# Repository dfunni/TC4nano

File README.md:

# TC4nano
The TC4nano is an Arduino Nano shield for termperature logging (up to 4 thermocouples) and PID control of a resistive heating element for use in home coffee roasting (based off of the TC4 Arduino Uno shield design copyright 2014 MLG Properties LLC and bvwelch.com CC-BY). The TC4nano includes one onboard SSR for heater control via slow PWM. Forced air is recommended for cooling the SSR in configurations drawing 10A or above.

### CONTENTS:
1. Configuring Artiasn
2. Updating TC4 Firmware
3. Troubleshooting

The TC4nano is pre-configured for the Artisan roaster-scope software using the aArtisanQ_PID_6_2_3 by Jim Gallt and Brad
Collins provided under BSD Liscense.

TC4 firmware can be found at:
https://github.com/greencardigan/TC4-shield

Artisan can be found at:	
https://github.com/artisan-roaster-scope

Artisan installation instructions:
https://github.com/artisan-roaster-scope/artisan/blob/master/wiki/Installation.md

## 1. CONFIGURING ARTISAN

### General Config
The configuration below assumes use with Poppery I roaster and no fan control through Artisan. 

For Poppery II or other DC fan systems, fan control can be added by connecting a DC motor driver to the IO3 jumper. For AC fan control, zero cross detection circuitry and an additional random fire SSR are required as well as reflashing the Arduino firmware with different configuration settings. For Artisan configuration with fan control see the setup described here: https://www.youtube.com/watch?v=0-Co-pXF2NM. 

#### Config > Device...

ET/BT tab:
- select TC4 radio button
- ET Channel - 2
- BT Channel - 1
- AT Channel - None
- PID Firmware - unchecked
- Control - checked
- Curves: ET - unchecked BT - checked
- LCDs: ET - unchecked BT - checked Swap - unchecked

Extra Devices tab:
- Add two devices

Device 1: 
- Device - ArduinoTC4 56 
- Label1 - "Heater" 

Device 2:
- Device - ArduinoTC4 78
- Label1 - "SV" 
- Label2 - "AT"

Note: after clicking "OK" in the Device menu the Port menu will automatically pop up. Prior to each roast session ensure the port reflects the correct Arduino.

#### Config > Sampling Interval 
- set to "1.0" seconds

#### Config > Curves... > RoR tab
- check the boxes for curves and LCDs you want to view and check projection

#### Config > Events

Config tab:
- Annotations - check
- 1 - uncheck - Fan
- 2 - check - Heater
- 3 - uncheck - Damper
- 4 - uncheck - Burner
- Auto CHARGE/Auto Drop/Mark MET/Show Time Guide - uncheck

Buttons tab:
- add one button
- Label - "Heater Off"
- Type - Heater
- Value - 0
- Action - Serial Command
- Documentation - "OT1;0"
- Visibility - ON

Sliders tab:
- In the heater row set the following to:
- Heater - check
- Action - Serial Command
- Command - "OT1;{}"
- Offset - 0.0
- Factor - 1
- Min - 0
- Max - 100
- Fan - uncheck
- Damper - uncheck
- Burner - uncheck

#### Config > Temperature
- Select Fahrenheit or Celcius mode

### PID Config

Click the blue CONTROL button (ensure Control is checked under Config > Device)

Recommended starting PID parameters:

|            | kp  | ki   | kd  |
|------------|-----|------|-----|
| Poppery I  | 2.2 | 0.08 | 20  |
| Poppery II | 1.3 | 0.06 | 4.5 |

- Source - BT

Target:
- Positive - Heater
- Negative - None

Set Value:
- Mode - Background (ensure background profile is loaded prior to roasting)
- Lookahead - 10s (adjust as necessary)

- Start PID on CHARGE - check

### Creating a Profile

#### Tools > Designer

Adjust the circles to the desired locations, add or delete points as necessary.

When profile is complete go to Tools > Designer (uncheck) and proile will be
loaded onto the graph.

Hit the RESET button, then save the profile to your Profiles directory.

### Loading a Background Profile

#### Roast > Background

- Show - check
- BT - check
- All others - uncheck
- Align - CHARGE
- Load - select a saved profile from your profile directory

## 2. UPDATING TC4 FIRMWARE

The latest version of the TC4 firmware can be found on github. Version 
6.6 zip file can be found at:
https://github.com/greencardigan/TC4-shield/tree/master/applications/Artisan/aArtisan_PID/tags/REL_aArtisanQ_PID_6_6

Once downloaded open aArtisanQ_PID.ino in the Arduino IDE 
(https://www.arduino.cc). This will open all of the other files from the
aArtisanQ_PID folder as seperate tabs in the IDE.

Select the user.h tab and to choose the options you wish to enable by 
uncommenting/commenting the options in this file.

- Under "Base configuration" ensure CONFIG_PWM is selected as the 
TC4nano does not include a ZCD.

- Under "Tempreature Unit" comment out CELCIUS if Fahrenhiet is desired.

When all appropriate changes are made, connect the Arduino to the computer and
select the following settings from the menu bar:

- Tools > Board > Arduino Nano
- Tools > Processor > ATMega328P (Old Bootloader)
- Tools > Port > /dev/cu.YOUR_ARDUINO

Finally, flash the Adduino Nano by clicking the upload (forward arrow) button 
in the Arduino IDE. A display of the progress will appear in the command prompt
at the bottom of the IDE and "Done Uploading" will display when it completes 
sucessfully.

## 3. TROUBLESHOOTING:

### Generic Arduino Not Recognized (macOS)

Copy and paste these commands into terminal one by one 
(to open terminal press command+space and type 'terminal', then hit enter):

First check to see if homebrew is installed

    brew --version

If it is not installed (ie you get an output that is something other than
the version of homebrew) run the following commmand

    /usr/bin/ruby -e "$(curl -fsSL https://raw.githubusercontent.com/Homebrew/install/master/install)"

Then run the following two commands to install the CH34x drivers needed
to use the generic arduino nano

    brew tap mengbo/ch340g-ch34g-ch34x-mac-os-x-driver https://github.com/mengbo/ch340g-ch34g-ch34x-mac-os-x-driver
    brew cask install wch-ch34x-usb-serial-driver

Now restart your computer, and see if Artisan recognizes the arduino.
Alternately, you can enter the following in the terminal and look for an output
that is not an error.

    ls /dev/cu.usb* /dev/cu.wch*

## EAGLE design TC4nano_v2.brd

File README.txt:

# TC4nano
The configuration specified in this document is for the TC4nano which uses
one SSR for heater control (no fan control) and logs BT only.

CONTENTS:
Configuring Artiasn
- General Config
- PID Config
- Creating a Profile
- Loading a Background Profile
Updating TC4 Firmware
Troubleshooting
- Generic Arduino Nano Not Recognized

The TC4nano is configured for the Artisan roaster-scope software. The latest 
version can be found at:	
https://artisan-roasterscope.blogspot.com

Artisan installation instructions:
https://github.com/artisan-roaster-scope/artisan/blob/master/wiki/Installation.md

The TC4nano comes preloaded with aArtisanQ_PID_6_2_3 by Jim Gallt and Brad
Collins and is provided under BSD Liscense. 

The provided firmware has been tested with Artisan versions up to 1.5. 
If you wish to update the firmware the instructions are provided below.

*******************************************************************************

CONFIGURING ARTISAN

Leave defaults unless specified below. Text input is listed in " ".

===============================================================================
General Config
---------------------------------
Config > Device...

> ET/BT tab:
select TC4 radio button
ET Channel - 1
BT Channel - 2
AT Channel - None
PID Firmware - unchecked
Control - checked
Curves: ET - unchecked BT - checked
LCDs: ET - unchecked BT - checked Swap - unchecked

> Extra Devices tab:
Add two devices

Device 1: 
Device - ArduinoTC4 56 
Label1 - "Heater" 
Label2 - "Fan"

Device 2:
Device - ArduinoTC4 78
Label1 - "SV" 
Label2 - "AT"
OK

Note: after clicking "OK" in the Device menu the Port menu will automatically
pop up. Leave this as default for now. When roasting ensure the port reflects
the TC4's Arduino.
OK
---------------------------------

Config > Sampling Interval 
set to "1.0" seconds
OK
---------------------------------

Config > Curves... > RoR tab
check the boxes for curves and LCDs you want to view and check projection
OK
---------------------------------

Config > Events

> Config tab:
Annotations - check
1 - check - "Fan"
2 - check - "Heater"
3 - uncheck
4 - uncheck
Auto CHARGE/Auto Drop/Mark MET/Show Time Guide - uncheck

> Buttons tab
add one button
Label - "Fan Off"
Type - Fan
Value - 0
Action - Serial Command
Documentation - "IO3;0"
Visibility - ON

> Sliders tab
In the heater row set the following to:
Heater - check
Action - Serial Command
Command - "OT1;{}"
Offset - 0.0
Factor - 1
Min - 0
Max - 100

Fan - uncheck
Damper - uncheck
Burner - uncheck
OK
---------------------------------
Config > Temperature
Select Fahrenheit or Celcius mode
OK
---------------------------------

===============================================================================
PID Config

Click the blue CONTROL button (ensure Control is checked under Config > Device)

For Poppery I a good starting point is:
kp = 2.2; ki = 0.08; kd = 20

For Poppery II start with:
kp = 1.3; ki = 0.06; kd = 4.5

Source - BT

Target:
Positive - Heater
Negative - None

Set Value:
Mode - Background (ensure background profile is loaded prior to roasting)
Lookahead - 10s (adjust as necessary)

Start PID on CHARGE - check
OK

===============================================================================
Creating a Profile

Tools > Designer

Adjust the circles to the desired locations, add or delete points as necessary.

When profile is coplete go to Tools > Designer (uncheck) and proile will be
loaded onto the graph.

Hit the RESET button, then save the profile to your Profiles directory.

===============================================================================
Loading a Background Profile

Roast > Background

Show - check
BT - check
All others - uncheck
Align - CHARGE
Load - select a saved profile from your profile directory
OK

*******************************************************************************

UPDATING TC4 FIRMWARE

The latest version of the TC4 firmware can be found on github. Version 
6.6 zip file can be found at:
https://github.com/greencardigan/TC4-shield/tree/master/applications/Artisan/aArtisan_PID/tags/REL_aArtisanQ_PID_6_6

Once downloaded open aArtisanQ_PID.ino in the Arduino IDE 
(https://www.arduino.cc). This will open all of the other files from the
aArtisanQ_PID folder as seperate tabs in the IDE.

Select the user.h tab and to choose the options you wish to enable by 
uncommenting/commenting the options in this file.

- Under "Base configuration" ensure CONFIG_PWM is selected since the 
TC4nano does not include a ZCD.

- Under "Tempreature Unit" comment out CELCIUS if Fahrenhiet is desired.

- Leave all 4 "TC_TYPEx typeK" enabled under "Thermocouple Input Options"
even though only one thermocouple will be used.

- Ensure Baud rate of BAUD 115200

When all appropriate changes are made, connect the arduino to the computer and
select the following options from the menu bar:

Tools > Board > Arduino Nano
Tools > Processor > ATMega328P (Old Bootloader)
Tools > Port > /dev/cu.YOUR_ARDUINO

Finally, flash the Adduino Nano by clicking the upload (forward arrow) button 
in the Arduino IDE. A display of the progress will appear in the command prompt
at the bottom of the IDE and "Done Uploading" will display when it completes 
sucessfully.

*******************************************************************************

TROUBLESHOOTING:

===============================================================================
Generic Arduino Not Recognized

Copy and paste these commands into terminal one by one 
(to open terminal press command+space and type terminal, then hit enter):

First check to see if homebrew is installed

_______________________________________________________________________________
brew -v
_______________________________________________________________________________

If it is not installed (ie you get an output that is something other than
the version of homebrew) run the following commmand... this takes a while

_______________________________________________________________________________
/usr/bin/ruby -e "$(curl -fsSL https://raw.githubusercontent.com/Homebrew/install/master/install)"
_______________________________________________________________________________

Then run the following two commands to install the CH34x drivers needed
to use the generic arduino nano

_______________________________________________________________________________
brew tap mengbo/ch340g-ch34g-ch34x-mac-os-x-driver https://github.com/mengbo/ch340g-ch34g-ch34x-mac-os-x-driver
_______________________________________________________________________________

_______________________________________________________________________________
brew cask install wch-ch34x-usb-serial-driver
_______________________________________________________________________________

Now restart your computer, and see if Artisan recognizes the arduino.
Or you can enter the following in the terminal and look for an output
that is not an error.

_______________________________________________________________________________
ls /dev/cu.usb* /dev/cu.wch*
_______________________________________________________________________________

===============================================================================

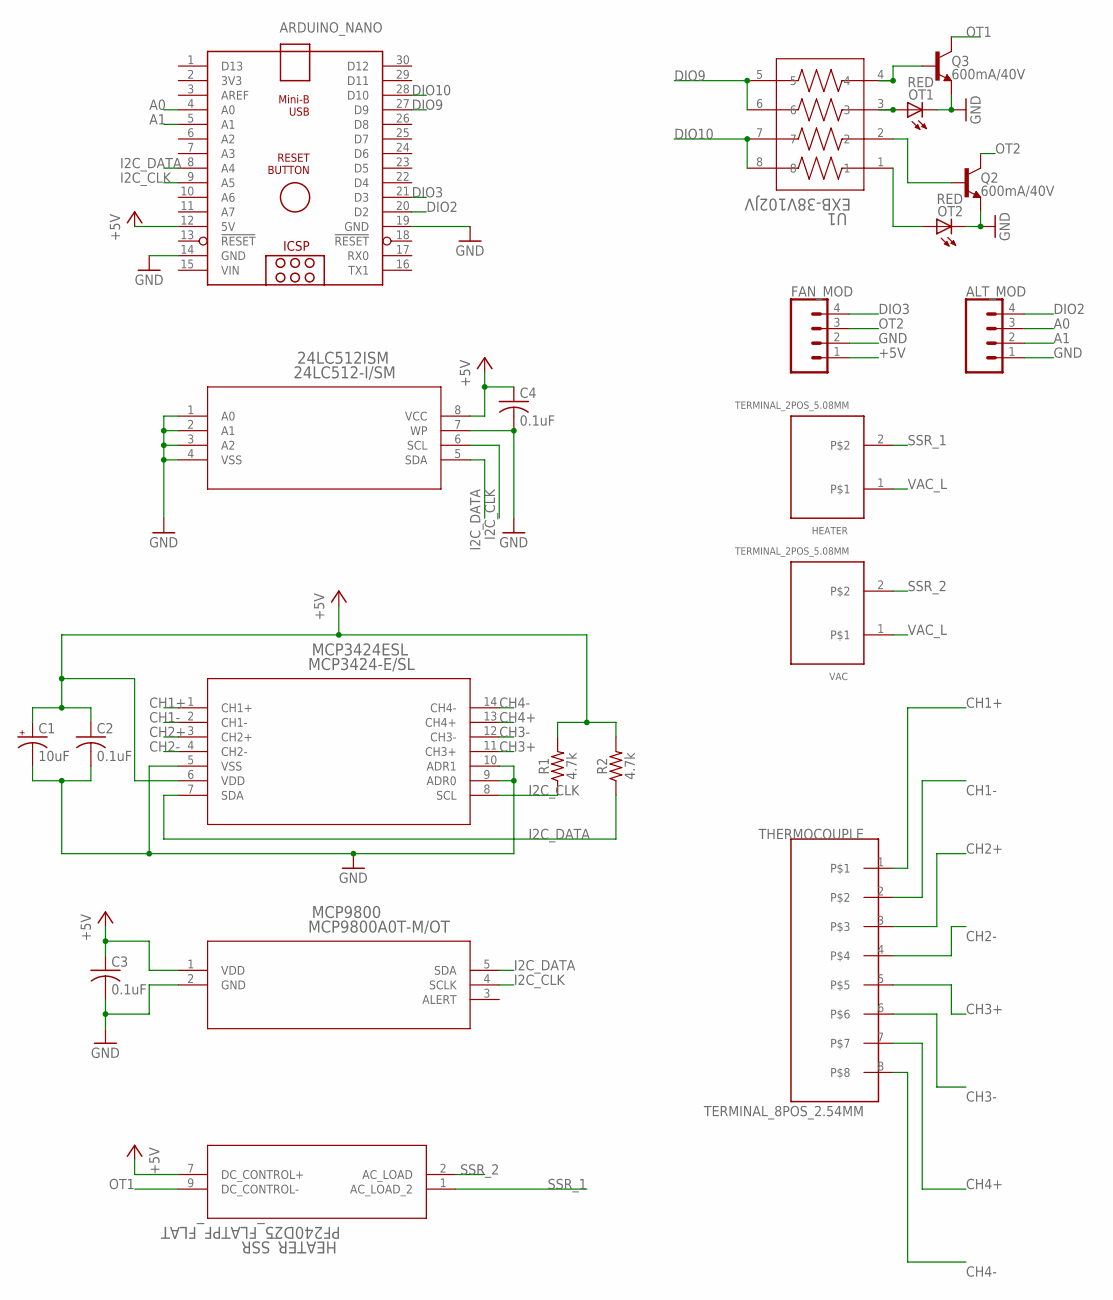
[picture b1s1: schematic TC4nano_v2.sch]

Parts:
24LC512ISM: 24LC512-I/SM; SOIC8-W_MC
ALT_MOD: CONN_04LONGPADS; 1X04_LONGPADS
ARDUINO_NANO: ARDUINO_NANO
C1: 10uF; EIA3216
C2, C3, C4: 0.1uF; C0805
FAN_MOD: CONN_04LONGPADS; 1X04_LONGPADS
HEATER: TERMINAL_2POS_5.08MM
HEATER_SSR: PF240D25_FLATPF_FLAT; RELAY_PF_FLAT
MCP3424ESL: MCP3424-E/SL; SOIC14-N_MC
MCP9800: MCP9800A0T-M/OT; SOT-23-5_MC
OT1, OT2: RED; CHIPLED_0805
Q2, Q3: 600mA/40V; SOT23-3
R1, R2: 4.7k; 0603
THERMOCOUPLE: TERMINAL_8POS_2.54MM
U1: EXB-38V102JV; C_ARRAY_EXB38V
VAC: TERMINAL_2POS_5.08MM

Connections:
+5V: 24LC512ISM.8 (VCC), ARDUINO_NANO.12 (5V), C1.+, C2.1, C3.1, C4.1, FAN_MOD.1, HEATER_SSR.7 (DC_CONTROL+), MCP3424ESL.6 (VDD), MCP9800.1 (VDD), R1.2, R2.2
A0: ALT_MOD.3, ARDUINO_NANO.4 (A0)
A1: ALT_MOD.2, ARDUINO_NANO.5 (A1)
CH1+: MCP3424ESL.1 (CH1+), THERMOCOUPLE.1
CH1-: MCP3424ESL.2 (CH1-), THERMOCOUPLE.2
CH2+: MCP3424ESL.3 (CH2+), THERMOCOUPLE.3
CH2-: MCP3424ESL.4 (CH2-), THERMOCOUPLE.4
CH3+: MCP3424ESL.11 (CH3+), THERMOCOUPLE.5
CH3-: MCP3424ESL.12 (CH3-), THERMOCOUPLE.6
CH4+: MCP3424ESL.13 (CH4+), THERMOCOUPLE.7
CH4-: MCP3424ESL.14 (CH4-), THERMOCOUPLE.8
DIO2: ALT_MOD.4, ARDUINO_NANO.20 (D2)
DIO3: ARDUINO_NANO.21 (D3), FAN_MOD.4
DIO9: ARDUINO_NANO.27 (D9), U1.5, U1.6
DIO10: ARDUINO_NANO.28 (D10), U1.7, U1.8
GND: 24LC512ISM.1 (A0), 24LC512ISM.2 (A1), 24LC512ISM.3 (A2), 24LC512ISM.4 (VSS), 24LC512ISM.7 (WP), ALT_MOD.1, ARDUINO_NANO.14 (GND), ARDUINO_NANO.19 (GND), C1.-, C2.2, C3.2, C4.2, FAN_MOD.2, MCP3424ESL.5 (VSS), MCP3424ESL.9 (ADR0), MCP3424ESL.10 (ADR1), MCP9800.2 (GND), OT1.C, OT2.C, Q2.2 (E), Q3.2 (E)
I2C_CLK: 24LC512ISM.6 (SCL), ARDUINO_NANO.9 (A5), MCP3424ESL.8 (SCL), MCP9800.4 (SCLK), R1.1
I2C_DATA: 24LC512ISM.5 (SDA), ARDUINO_NANO.8 (A4), MCP3424ESL.7 (SDA), MCP9800.5 (SDA), R2.1
unnamed: Q2.1 (B), U1.2
unnamed: OT2.A, U1.1
unnamed: Q3.1 (B), U1.4
unnamed: OT1.A, U1.3
OT1: HEATER_SSR.9 (DC_CONTROL-), Q3.3 (C)
OT2: FAN_MOD.3, Q2.3 (C)
SSR_1: HEATER.2, HEATER_SSR.1 (AC_LOAD_2)
SSR_2: HEATER_SSR.2 (AC_LOAD), VAC.2
VAC_L: HEATER.1, VAC.1
VIN: ARDUINO_NANO.15 (VIN)

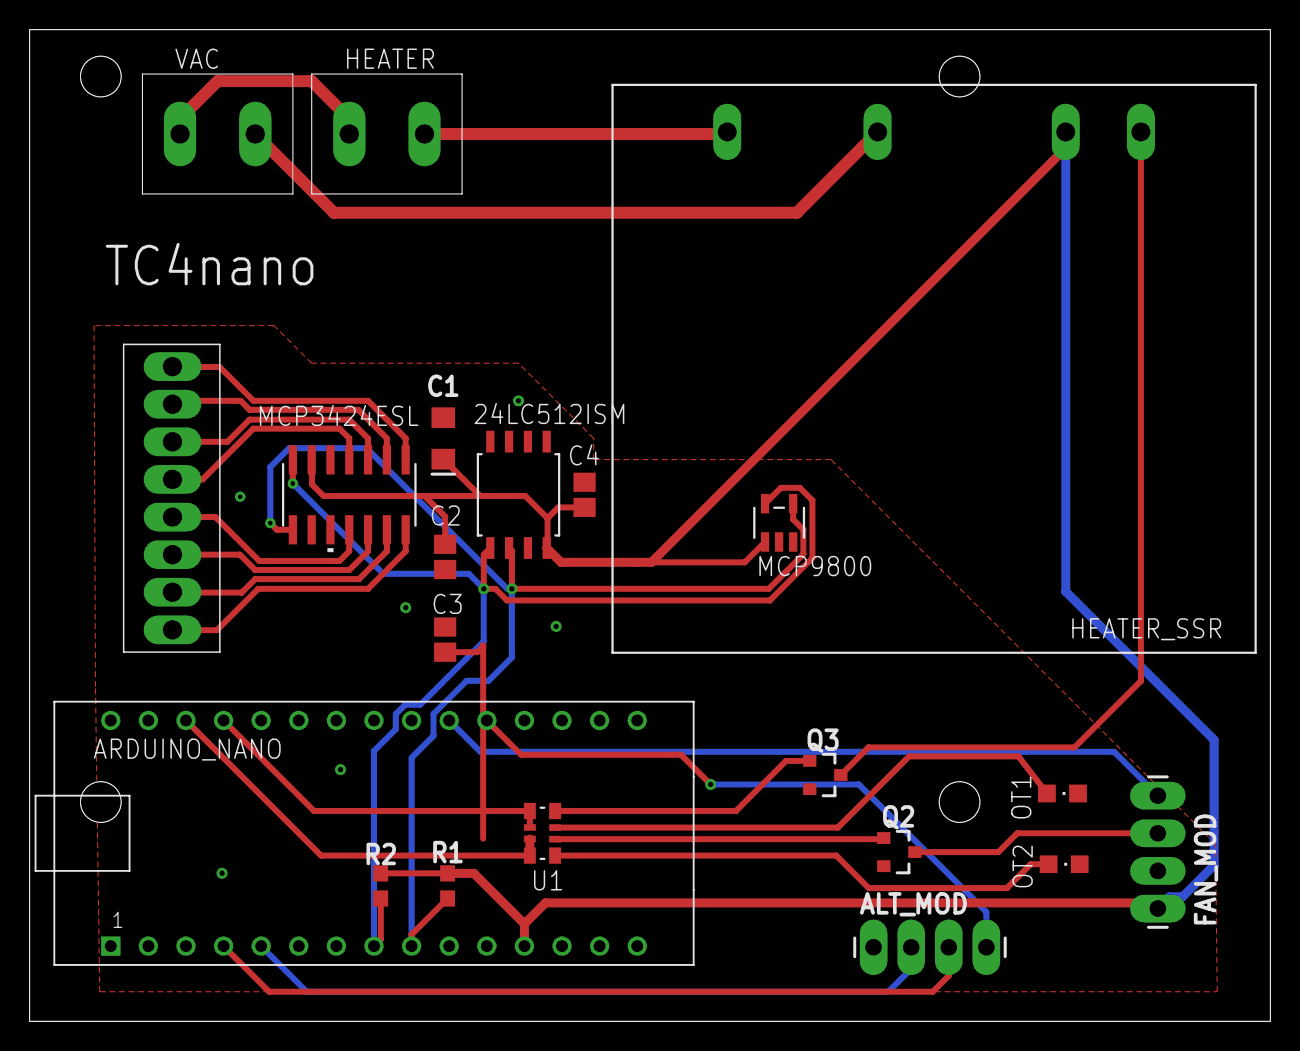
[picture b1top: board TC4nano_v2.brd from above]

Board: 2 copper layers, 83.8 x 67.0 mm, 21 parts (0 on the bottom side), 27 nets.

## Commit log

2018-11-17 Rename README.md to README.txt

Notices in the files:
parts and their libraries:
SparkFun-Capacitors: Licensing: Creative Commons ShareAlike 4.0 International - https://creativecommons.org/licenses/by-sa/4.0
